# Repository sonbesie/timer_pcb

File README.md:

# Timer: Printed Circuit Board (PCB)

## Description
A personal project built around a PIC microcontroller that enables or disables current flow through two independent circuits. The circuit is controlled from a computer through a USB Type-B port. This project is in the process of being modified to include two current sensors as well as an Ethernet port for data and power.

## Open
To open the project download KiCad and open the .pro file.

## Image

A render of the PCB is provided below:

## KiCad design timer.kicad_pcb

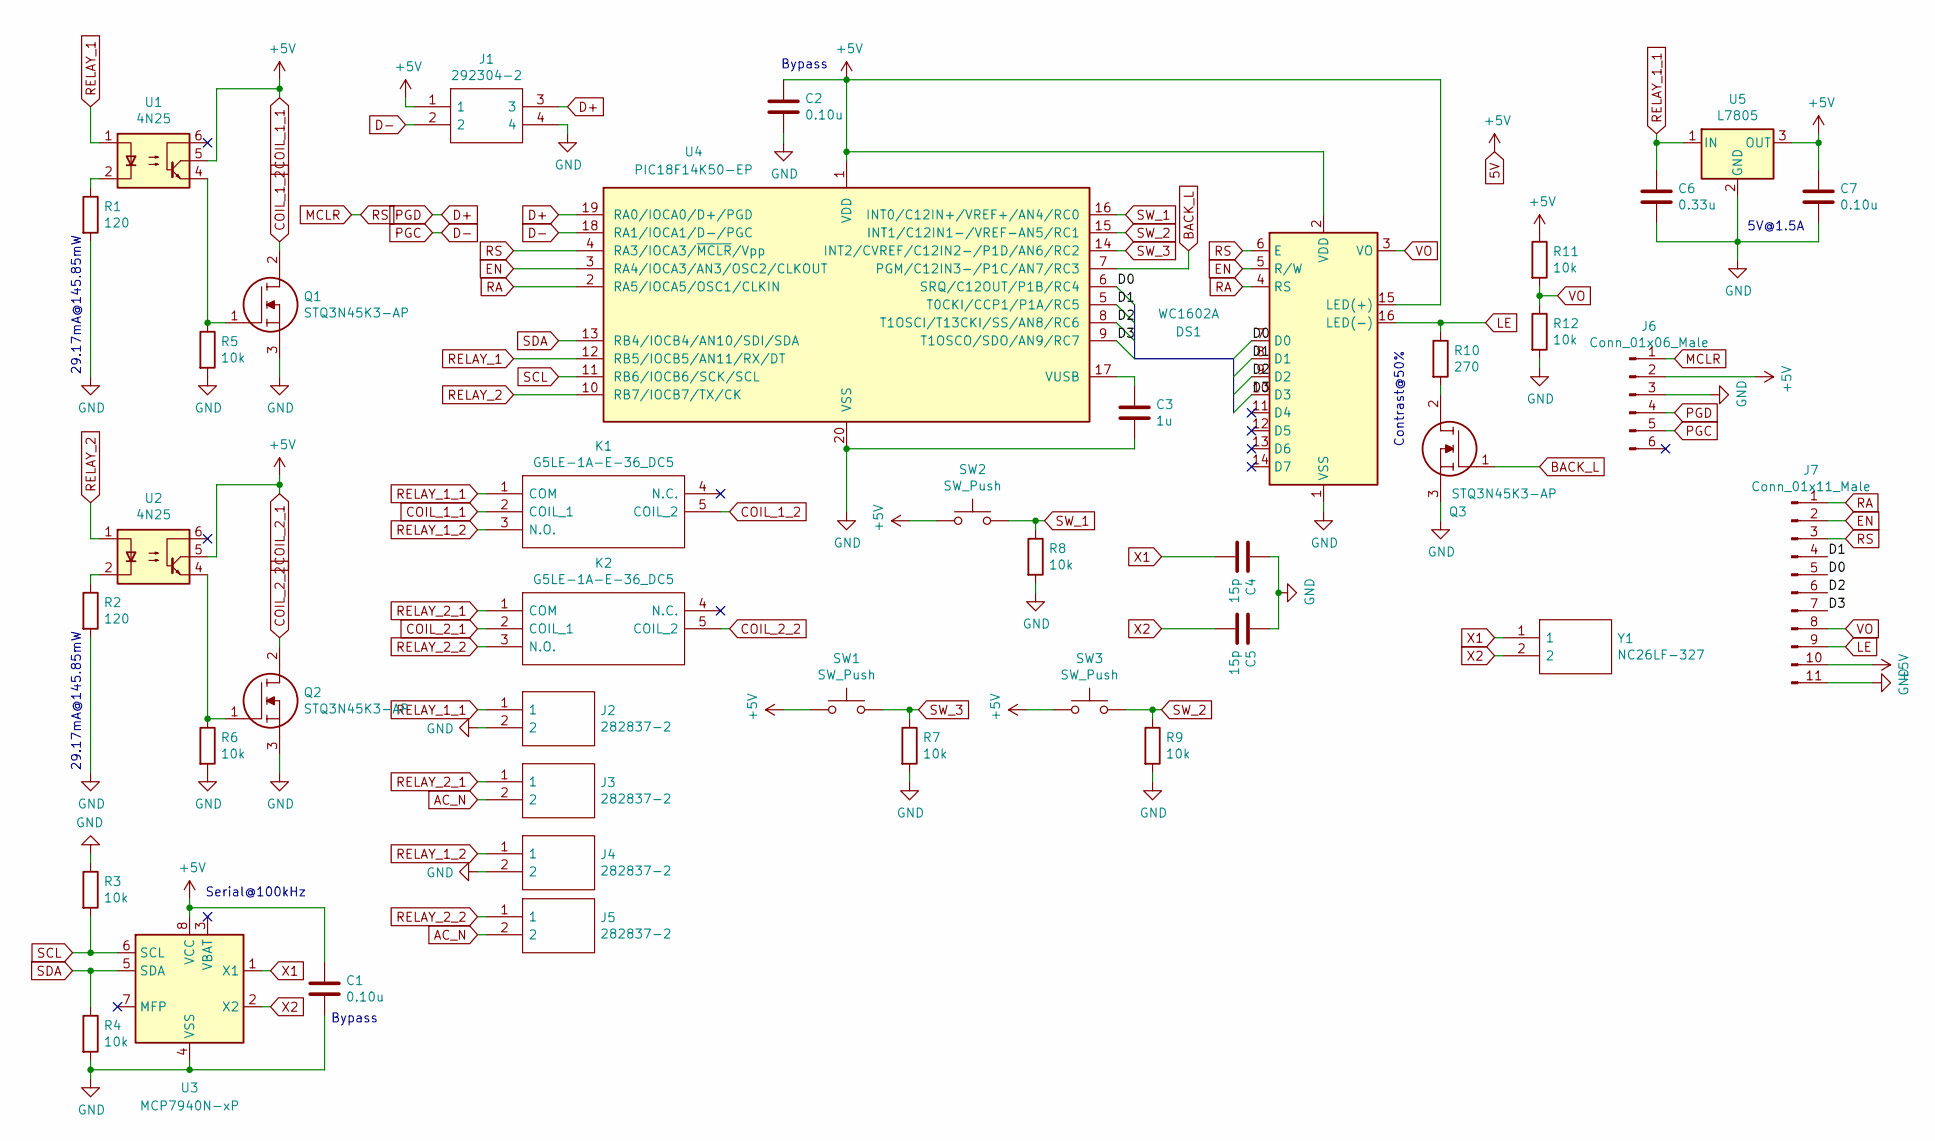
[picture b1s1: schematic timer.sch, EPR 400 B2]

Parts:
C1, C2, C7: 0.10u; C_Disc_D5.0mm_W2.5mm_P2.50mm
C3: 1u; C_Disc_D5.0mm_W2.5mm_P2.50mm
C4, C5: 15p; C_Disc_D5.0mm_W2.5mm_P2.50mm
C6: 0.33u; C_Disc_D5.0mm_W2.5mm_P2.50mm
DS1: WC1602A
J1: 292304-2; 292304
J2, J3, J4, J5: 282837-2; SHDR2W100P0X508_1X2_1016X820X1030P; Manufacturer_Part_Number 282837-2; Mouser Part Number 571-2828372
J6: Conn_01x06_Male; PinHeader_1x06_P2.54mm_Vertical
J7: Conn_01x11_Male; PinHeader_1x11_P2.54mm_Vertical
K1, K2: G5LE-1A-E-36_DC5; G5LE1AE36DC5; Manufacturer_Part_Number G5LE-1A-E-36 DC5; Mouser Part Number 653-G5LE-1A-E-36DC5
Q1, Q2, Q3: STQ3N45K3-AP; TO-92_Inline_Wide; Manufacturer_Part_Number STQ3N45K3-AP; Mouser Part Number 511-STQ3N45K3-AP
R1, R2: 120; R_Axial_DIN0207_L6.3mm_D2.5mm_P7.62mm_Horizontal
R3, R4, R5, R6, R7, R8, R9, R11, R12: 10k; R_Axial_DIN0207_L6.3mm_D2.5mm_P7.62mm_Horizontal
R10: 270; R_Axial_DIN0207_L6.3mm_D2.5mm_P7.62mm_Horizontal
SW1, SW2, SW3: SW_Push; SW_PUSH_6mm_H5mm
U1, U2: 4N25; DIP-6_W7.62mm
U3: MCP7940N-xP; DIP-8_W7.62mm
U4: PIC18F14K50-EP; DIP-20_W7.62mm
U5: L7805; TO-220-3_Vertical
Y1: NC26LF-327; Manufacturer_Part_Number NC26LF-327; Mouser Part Number 559-NC26-LF

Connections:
5V: C1.1, C2.1, C7.1, DS1.2 (VDD), DS1.15 (LED(+)), J1.1, J6.2, J7.10, K1.2 (COIL_1), K2.2 (COIL_1), R11.1, SW1.1, SW2.1, SW3.1, U1.5, U2.5, U3.8 (VCC), U4.1 (VDD), U5.3 (OUT)
/D0: DS1.7 (D0), J7.5, U4.6 (SRQ/C12OUT/P1B/RC4)
/D1: DS1.8 (D1), J7.4, U4.5 (T0CKI/CCP1/P1A/RC5)
/D2: DS1.9 (D2), J7.6, U4.8 (T1OSCI/T13CKI/SS/AN8/RC6)
/D3: DS1.10 (D3), J7.7, U4.9 (T1OSCO/SDO/AN9/RC7)
AC_N: J3.2, J5.2
BACK_L: Q3.1, U4.7 (PGM/C12IN3-/P1C/AN7/RC3)
COIL_1_2: K1.5 (COIL_2), Q1.2
COIL_2_2: K2.5 (COIL_2), Q2.2
D+: J1.3, J6.4, U4.19 (RA0/IOCA0/D+/PGD)
D-: J1.2, J6.5, U4.18 (RA1/IOCA1/D-/PGC)
EN: DS1.5 (R/W), J7.2, U4.3 (RA4/IOCA3/AN3/OSC2/CLKOUT)
GND: C1.2, C2.2, C3.2, C4.1, C5.1, C6.2, C7.2, DS1.1 (VSS), J1.4, J2.2, J4.2, J6.3, J7.11, Q1.3, Q2.3, Q3.3, R1.2, R2.2, R3.1, R4.2, R5.2, R6.2, R7.2, R8.2, R9.2, R12.2, U3.4 (VSS), U4.20 (VSS), U5.2 (GND)
LE: DS1.16 (LED(-)), J7.9, R10.1
MCLR: DS1.6 (E), J6.1, J7.3, U4.4 (RA3/IOCA3/~MCLR~/Vpp)
unnamed: C3.1, U4.17 (VUSB)
unnamed: Q1.1, R5.1, U1.4
unnamed: Q2.1, R6.1, U2.4
unnamed: Q3.2, R10.2
unnamed: R1.1, U1.2
unnamed: R2.1, U2.2
RA: DS1.4 (RS), J7.1, U4.2 (RA5/IOCA5/OSC1/CLKIN)
RELAY_1: U1.1, U4.12 (RB5/IOCB5/AN11/RX/DT)
RELAY_1_1: C6.1, J2.1, K1.1 (COM), U5.1 (IN)
RELAY_1_2: J4.1, K1.3 (N.O.)
RELAY_2: U2.1, U4.10 (RB7/IOCB7/TX/CK)
RELAY_2_1: J3.1, K2.1 (COM)
RELAY_2_2: J5.1, K2.3 (N.O.)
SCL: R3.2, U3.6 (SCL), U4.11 (RB6/IOCB6/SCK/SCL)
SDA: R4.1, U3.5 (SDA), U4.13 (RB4/IOCB4/AN10/SDI/SDA)
SW_1: R8.1, SW2.2, U4.16 (INT0/C12IN+/VREF+/AN4/RC0)
SW_2: R9.1, SW3.2, U4.15 (INT1/C12IN1-/VREF-AN5/RC1)
SW_3: R7.1, SW1.2, U4.14 (INT2/CVREF/C12IN2-/P1D/AN6/RC2)
VO: DS1.3 (VO), J7.8, R11.2, R12.1
X1: C4.2, U3.1 (X1), Y1.1
X2: C5.2, U3.2 (X2), Y1.2

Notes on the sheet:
29.17mA@145.85mW
Serial@100kHz
Contrast@50%
5V@1.5A
Bypass

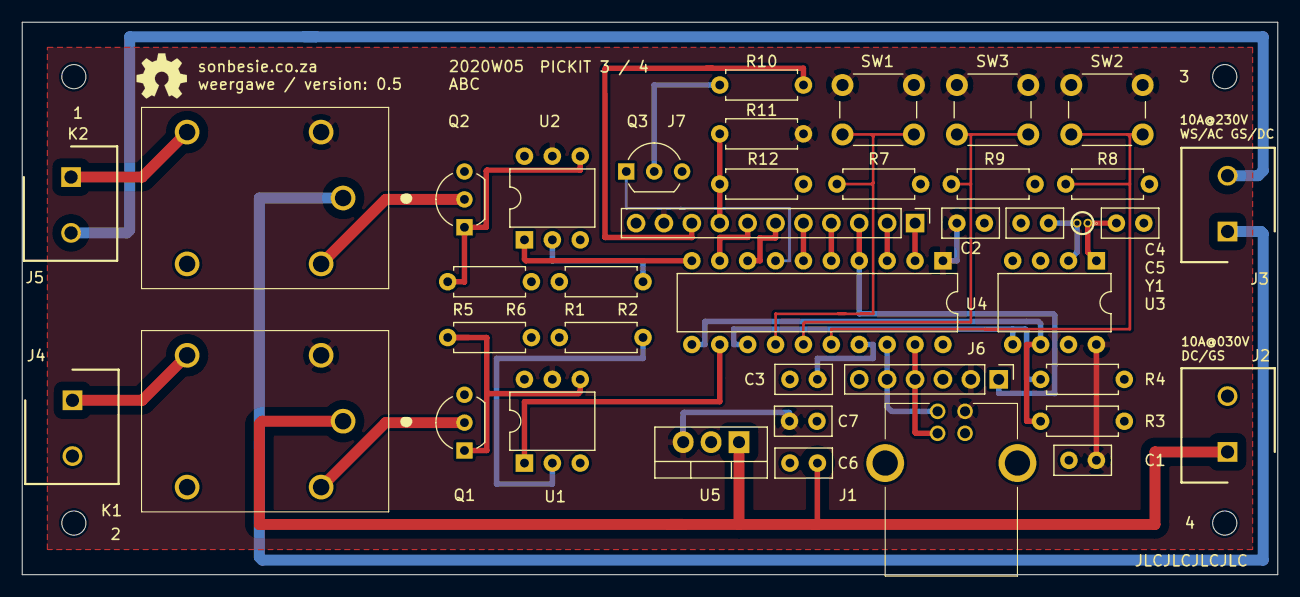
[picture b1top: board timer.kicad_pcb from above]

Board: 2 copper layers, 114.3 x 50.3 mm, 45 parts (0 on the bottom side), 36 nets.

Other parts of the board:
1, 2, 3, 4: MountingHole_2.2mm_M2
5: OSHW-Logo2_7.3x6mm_SilkScreen

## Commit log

2021-03-23 first github commit
2021-03-23 Create README.md
    first github commit
2021-03-23 Update README.md
    updated the pcb image
2021-03-23 Update README.md
    updated the readme file
